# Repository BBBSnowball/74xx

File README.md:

RISC-V core made of 7400-series logic
=====================================

We take the SERV RISC-V core and map it to 74xx logic with
tools that were intended for FPGA/ASIC synthesis. A PCB is
sort-of like an ASIC in 127000 nm technology, right?

Before you expect too much:
1. The example PCB has been designed for its artistic value.
   It won't work as-is (see below).
2. You can use the tools with your logic (Verilog, VHDL) but
   you may have to adjust the scripts a bit. In addition,
   some manual work in KiCad will be required, e.g. add
   connectors or LEDs.
3. The automated part is from Verilog to PCB. All further
   steps for the example image above are manual work in
   GIMP and Inkscape. See below for some info about that.

Why?
----

Olof was presenting the serv core at a virtual RISC-V meetup
in 2021. He mentioned that someone had converted it to 74xx
logic and the gate count was low enough that I just *might*
be able to afford building one. He pointed me to
[this](https://web.archive.org/web/20200930140306/https://twitter.com/ravenslofty/status/1311285303236268033)
Twitter thread by ravenslofty. Much of this project is based
on their idea.

It would be a lot of work to make a PCB that has enough educational
value to warant the cost, e.g. add RAM and peripherals and have some
programs that are small enough to somehow load onto the board and
then debug with a multimeter.

We revisited the project two years later with a more achievable
goal: Make a PCB that looks nice and sort-of could work.

How?
----

The usual small RISC-V cores need around 1000 LUT. [SERV][SERV] is
bit-serial, which is quite unusual for a 32-bit ISA, but it makes
the core really small (200 LUT).

[Yosys][Yosys] is used by most of the FOSS FPGA flows but you can point
it to other targets. Ravenslofty has created such a target description
("74xx-liberty", the main library file is in "liberty" format).
Pepijn de Vos has added scripts that convert the resulting netlist
into a KiCad schematic.

The algorithms in [Verilog to Routing][VTR]'s VPR were meant to place
and route logic in an FPGA but they will also unclutter our ratsnest
of connections. We only have to provide a description of our, ehm, "FPGA".
(It is field programmable if you bring your PineCil, isn't it?)

As this is for artistic value, we choose the aspect ratio of the FPGA
grid to fit A4 paper and there are some strategic cutouts.

We are only interested in placement but the result will be better when we
let it run routing passes anyway. The tool will generate an XML file that
tells us which gates have been combined into one logic element (i.e. one
74xx device in our case) and a text file with the positions of each
element in the grid. We generate a KiCad PCB file from that information
using [SKiDL][SKiDL].

Some parts are best designed in KiCad, e.g. keepout areas for artistic
reasons, and buttons+LEDs that should be in specific locations. Therefore,
we combine the generated parts with a template PCB.

Next, we need to route the ratsnest. We could try and use the routing
that has been generated by VPR but we don't do that, for now. Instead,
we let the [freerouting][freerouting] auto-router do all of the work.
It will finish within an hour or so if the placement is good (i.e. short
connections with not too many crossings) and if there is enough space.
If you add some huge keepout areas in the middle (why would anyone do
that? *cough*), it will stop making progress after some hours and not
finish even after days so it's best to restart with a more relaxed layout
in this case.

[SERV]: https://github.com/olofk/serv
[Yosys]: https://github.com/YosysHQ/yosys
[VTR]: https://github.com/verilog-to-routing/vtr-verilog-to-routing
[SKiDL]: https://github.com/devbisme/skidl
[freerouting]: https://github.com/freerouting/freerouting

Will the RISC-V actually work?
------------------------------

Sadly, no. And for more than one reason. Most of this is because we ran out
of time (and correct function was optional):

1. The keepout areas were too much for the auto-router. 200 connections (5%)
   are unrouted. It did work with an earlier version (`serv_top` without
   register file and no keepouts). We think that it will work with more space
   (and maybe run VPR a few times and see how the auto-router likes each placement).
2. The register file seems to use a synchronous RAM with heterogeneous widths
   and the polarity of some control signals doesn't match. We will have to
   provide a wrapper that adds the required glue logic.
3. Instruction and data bus are mapped to DIP switches and LEDs so the processor
   won't run very far unless you answer its questions for values from the RAM.
   This is technically a working processor and it sidesteps the issue of how
   we would bootstrap (i.e. load the initial program into RAM). The downside is
   that nobody will use it for very long. Any practical PCB would use something
   like the Servant SoC and add UART and a bootloader in ROM (or a large array
   of DIP switches - if you have plenty of time and money to spare).
4. Crosstalk may be an issue even at small speeds if we inject false edges into
   the clock or reset lines. Fortunately, these should be the only critical ones
   so some shielding (or buffers) should help if we run into problems with that.
   (I don't think freerouting can do shielding but we could increase trace width
   for the net class and later replace it by a smaller wire plus shields.)
5. We haven't simulated the result and what isn't tested usually doesn't work.
   I don't expect any significant bugs in the tools but plenty could be hiding
   in our scripts and target descriptions.
    - We already have models that should work for simulation (see `74_models.v`).
    - Proprietary ASIC flows use logic equivalence checks (Formality, Conformal).
      Yosys supports formal verification so [we could do the same](https://github.com/YosysHQ/eqy).
    - In either case, we have to map from PCB to Verilog netlist while avoiding
      doing the same errors as in the forward direction, e.g. swapped pins.
6. The image is scaled to A4 but the actual size is 510x353 mm, which is larger
   than A4 and even A3.

Other improvements that we omitted for lack of time:

- Let VPR determine the order and location or IO pads or add location constraints
  if the order is fixed.
- Tell VPR about the locations of pins in each logic element. We are currently
  telling it that pins can be swapped at will, which isn't really true.
- Use the routing info from VPR, e.g. increase grid spacing if routing channels
  are full. We could even generate wires for the routing so the auto-router has
  a working starting point for global routing (assuming that we omit connection stubs
  between routing channels and the actual devices pads because freerouting can probably
  do that better).
- Automatically call freerouting and import result.

How do I use it with my own logic?
----------------------------------

1. Install the tools.
    - If you have the Nix package manager, enable flakes and run `nix develop` in this repo.
    - Otherwise, have a look at `flake.nix` and install with a package manager of your choice.
2. Edit the scripts (optional but recommended):
    1. Point `kicad/Makefile` to your Verilog and/ or VHDL files.
        - Let's keep the "serv" name, for now, to keep it simple.
        - For VHDL, you will need Yosys with the GHDL plugin.
    2. Adjust the FPGA grid.
        - Change one of the `<fixed_layout>` nodes in `kicad/74xx_fpga.xml`
          and put its name into the Makefile after the `--device` parameter for VPR.
        - Keep the grid only a bit larger than necessary if you want to achieve high
            utilization (i.e. not so many unused gates).
        - Update the grid size argument for `generate_netlist2.py` in the Makefile.
            You can use the empty string to automatically use min/max occupied positions.
    3. Adjust the KiCad template (`kicad/serv_vpr_template.kicad_pcb`).
        - If you don't want any custom features for you PCB, you can pass an empty
          string to `generate_netlist2.py` instead of template file to not use any template.
        - We will use the auto-router anyway so there's no need to do manual routing
          for custom parts of the logic.
    4. Adjust `generate_netlist2.py` to change how the PCB is generated.
        - Grid spacing is defined in `mm_per_chip_x` and `mm_per_chip_y`.
        - Omit or move the capacitor.
        - Adjust position and layer of texts.
        - ...
3. Run `make all` (or `make out/serv_vpr_generated.kicad_pcb`). This will
   generate the PCB.
4. Run the auto-router.
    - Run `make serv-freerouting` to start the auto-router.
    - Pay attention to board edges. If part of the logic is outside the board, routing
      will never finish. If you do any manual changes in KiCad, don't forget to export
      the Spectra file, again.
    - Start auto-routing. It will usually need several passes before it has routed
      everything and then it will start optimization. If it doesn't seem to get any
      better anymore, left-click on the main area of the window to stop it. It will ask
      for confirmation and then it needs some time to actually stop.
    - Export the Spectra session and import it into KiCad.
5. Do the usual KiCad things, e.g. design rule check, export gerbers, ...

How to make a picture like the one above?
-----------------------------------------

This is not a complete guide because all of this were manual steps with lots of trial and error.

- KiCad: We have added some of the missing trace (that the auto-router could route). That's why the
  traces on the right look different.
- KiCad: Export -> SVG: F_Cu, B_C, F_Silk
    - Cu with colors, Silk in black&white
    - (reason not to export in black&white: hole in pads would be invisible (same color as the ring))
- KiCad: Open 3D view. Enable Raytracing. Export screenshots of top and bottom part of the PCB.
    - I had set many of the colors to semi-transparent for an earlier experiment but I think that I
      had undone that for the pictures.
- Load in Inkscape, select everything but background, export "Selection" to PNG with 600 dpi
    - I would like to keep it as a vector graphic but Inkscape becomes very slow.
- Import into GIMP:
    - invert colors
    - select by color with threshold 5%, click light-grey ring of a via, flood-fill with same color as the traces
    - add as layers to the same image
    - copy content of layer into layer mask, invert colors, use Colors->Curve to make the main color fully opaque
    - add a white background layer
    - copy bottom and upper part from renderings, adjust scale and position to match copper layers
- Colors and 3D effect for copper layers:
    - The geometry is in the layer mask so we can simple fill the whole layer with the desired color.
    - Fill F_Cu with Perlin noise: Filters -> Render -> Noise -> Perlin
      (I haven't written down the settings. Current settings are: alpha 1.2, scale 1.8, z -1.0, iterations 3)
    - Change color (done with Colors -> Colorize, I think).
    - Fill B_Cu with a darker shade of red.
    - Copy F_Cu, rename to "F_Cu shadow", between F_Cu and B_Cu, move down and right by a few pixels.
      Fill with a darker shade of red.
        - I had the layer mode set to "darken" and that looked a bit better. However, it was only applied
          to layers in the same group so that became an issue later.
- White background for Silk:
    - Layer mask to selection for Silk layer.
    - Add a new layer below Silk.
    - Grow and/ or feather the selection.
    - Fill whole selection with white.
    - Repeat with different settings until it looks right.
- Blend between copper and renderings:
    - Add silk layers to one layer group and copper layers to another.
    - It might make sense to do the same for the renderings (or combine them into one layer).
    - Extend rendering layers to image size.
    - Edit layer masks. Use gradient fill for the general shape of the blending.
    - Use airbrush tool for the details.
        - Make the edges of the blend not to straight.
        - Darken or remove copper over ICs and capacitors (at least were it looks strange).
        - Extend some of the copper traces over the renderings.
        - Silk is black in the middle part and white on the renderings. For any text that crosses the blending,
          make Silk layer opaque for that whole text.
- Add large digits:
    - select the wires and/ or areas in KiCad so they are painted in front of other things (e.g. airwires)
    - copy screenshot into GIMP
    - select wanted parts (select by color)
    - copy into main image as a new layer, adjust scale and position
    - select by color, feather by 50 px, fill with yellow, feather by 150 px (probably twice),
      fill with white (or very light yellow), choose sensible opacity for the layer
    - This is not just to make the inner ring of the zero visible but also to de-emphasize some tracks that
      run through the supposed keepout areas (because I had hoped that it would be able to route it without
      the keepouts but it didn't make much progress because any new trace would have to ripup lots of existing
      ones). Thus, it should be in front of the copper layers.
- Brighten area for prior work text:
    - Add a layer. Rectangular selection. Grow/feather. Fill with white. Set sensible opacity.
- Fixup texts on Silk:
    - Some important texts are hidden behind LEDs or missing (wrong layer?).
    - We didn't want to redo the renderings so we added texts in GIMP. Font is wrong, perspective is wrong, color
      doesn't quite match. Well, close enough.
- Add border:
    - The copper layers contain the board edge but that doesn't look nice.
    - The aspect ratio doesn't exactly match A4 so we will have some white space around our image. The renderings
      have a defined edge but the copper layers not so much.
    - Therefore, add a black border around everything.
- Export PNG
    - Use same DPI as before.
- Inkscape:
    - New A4 document.
    - Add the image and choose sensible page borders so the difference in aspect ratio is not too visible.
    - Add texts. The 7-segment font is [DSEG](https://www.keshikan.net/fonts-e.html).
    - Add QR code (`qrencode -t png -o qrcode.png 'https://github.com/BBBSnowball/74xx/tree/hans'`).
- Export text to GIMP:
    - This is only because further processing is out of our hands and we want to reduce risk. A PNG seems to
      be the safest bet with the image being mostly non-vector anyway.
    - Select the image. Set page size to content (i.e. the selected image).
    - Hide the image (using the "Layers and Objects" dialog).
    - Export to PNG using exactly the resolution of the image in GIMP.
      (DPI won't match because we have scaled the image in Inkscape.)
    - Add as a layer in GIMP.
    - Export PNG from GIMP.

The resulting XCF file is 500 MB in size so each download would be half of the free, monthly quota on Github.
We will have to find some other way to share it...

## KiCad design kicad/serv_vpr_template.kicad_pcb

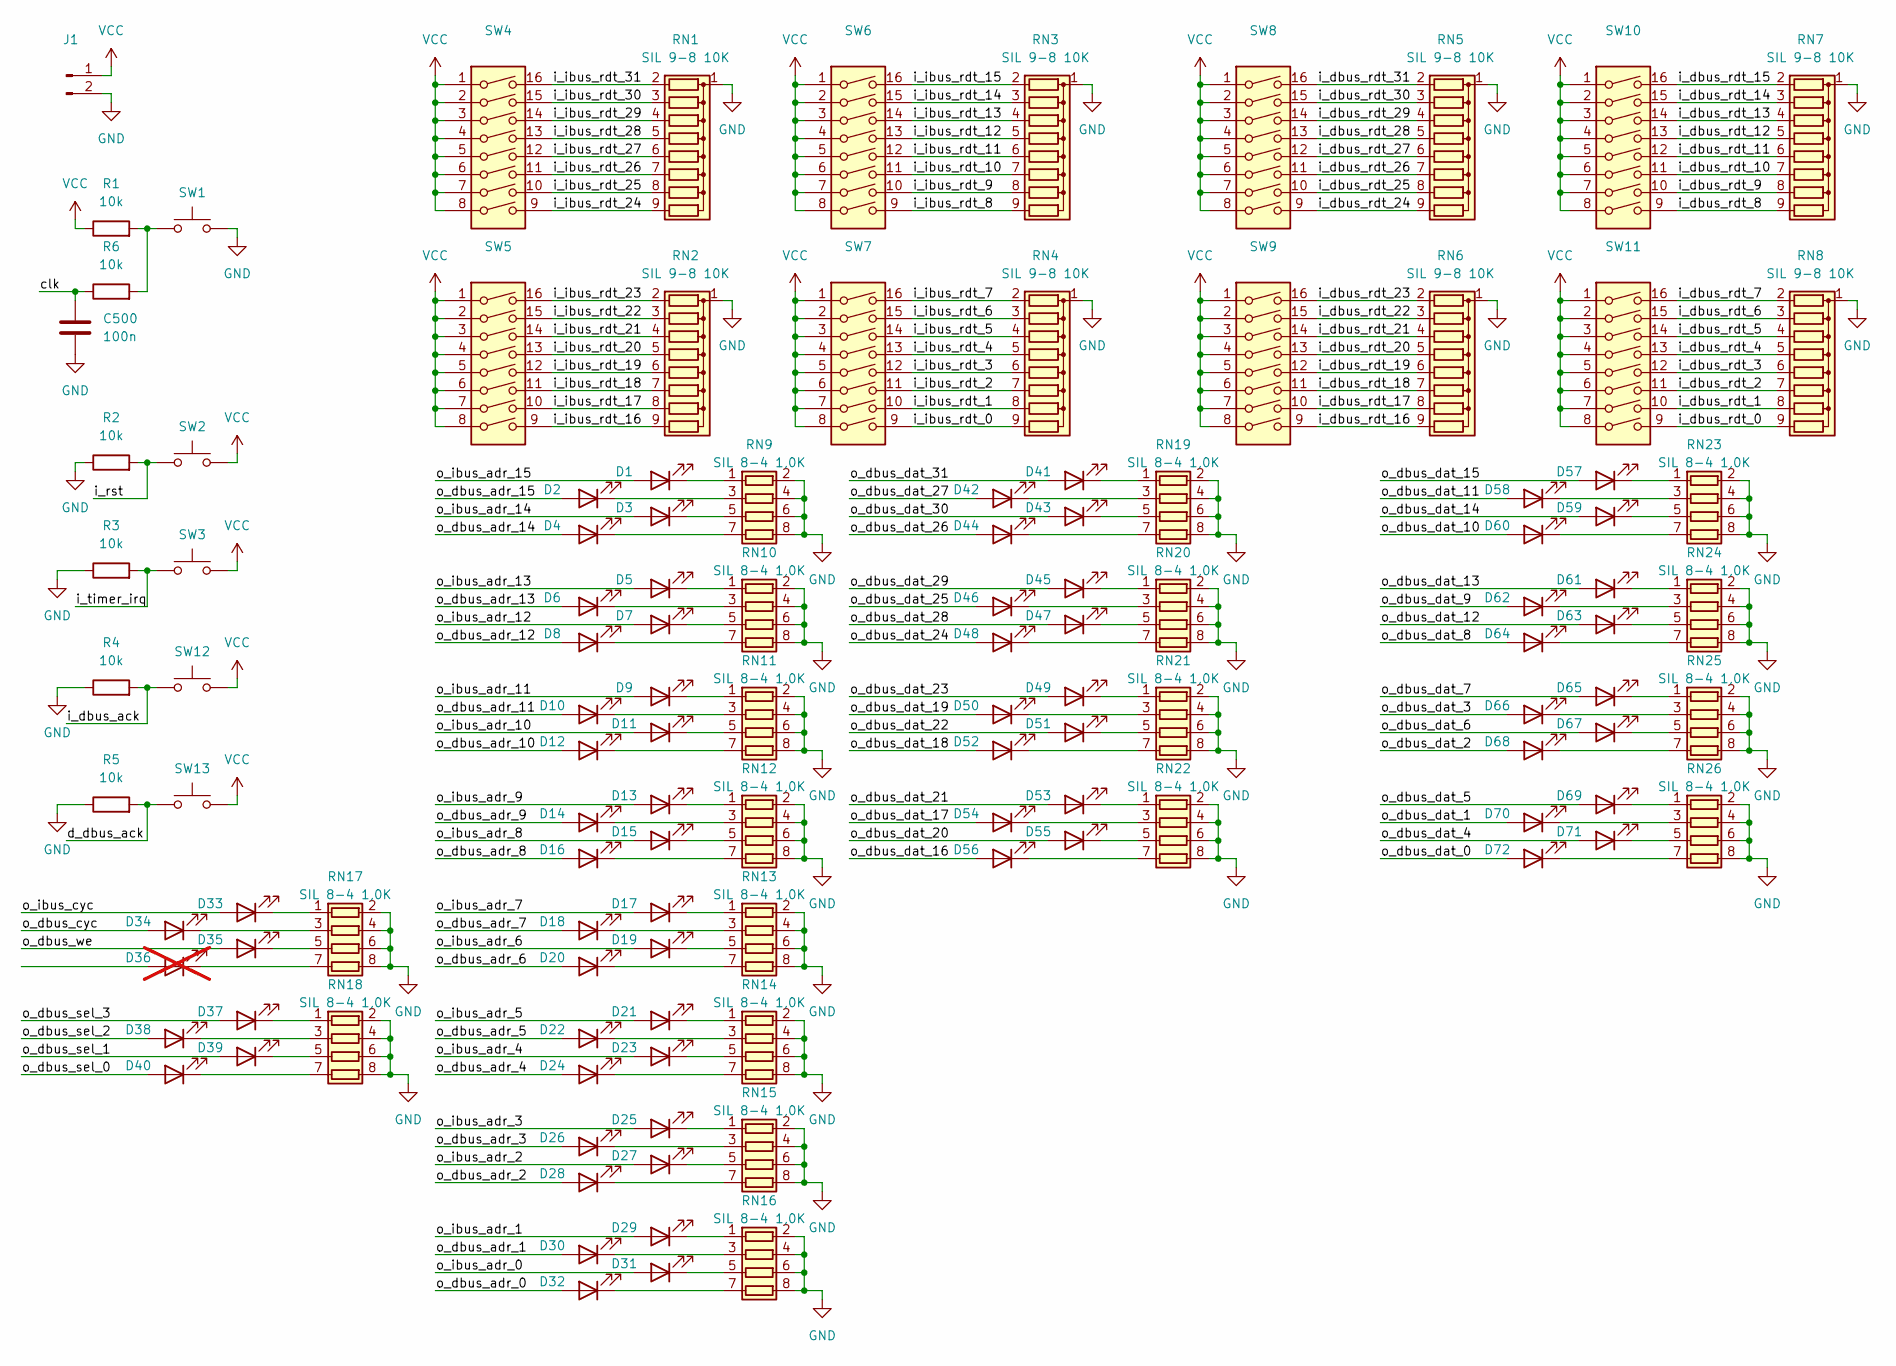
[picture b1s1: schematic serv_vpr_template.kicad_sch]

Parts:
C500: 100n; C_Disc_D5.1mm_W3.2mm_P5.00mm
D1, D2, D3, D4, D5, D6, D7, D8, D9, D10, D11, D12, D13, D14, D15, D16, D17, D18, D19, D20, D21, D22, D23, D24, D25, D26, D27, D28, D29, D30, D31, D32, D33, D34, D35, D37, D38, D39, D40, D41, D42, D43, D44, D45, D46, D47, D48, D49, D50, D51, D52, D53, D54, D55, D56, D57, D58, D59, D60, D61, D62, D63, D64, D65, D66, D67, D68, D69, D70, D71, D72: LED_D5.0mm
D36: LED_D5.0mm; not fitted
J1: Conn_01x02_Pin; Wago_734-132_1x02_P3.50mm_Vertical
R1, R2, R3, R4, R5, R6: 10k; R_Axial_DIN0207_L6.3mm_D2.5mm_P10.16mm_Horizontal
RN1, RN2, RN3, RN4, RN5, RN6, RN7, RN8: SIL 9-8 10K; R_Array_SIP9
RN9, RN10, RN11, RN12, RN13, RN14, RN15, RN16, RN17, RN18, RN19, RN20, RN21, RN22, RN23, RN24, RN25, RN26: SIL 8-4 1,0K; R_Array_SIP8
SW1, SW2, SW3, SW12, SW13: SW_PUSH_6mm_H5mm
SW4, SW5, SW6, SW7, SW8, SW9, SW10, SW11: SW_DIP_SPSTx08_Slide_9.78x22.5mm_W7.62mm_P2.54mm

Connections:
/clk: C500.1, R6.1
/d_dbus_ack: R5.2, SW13.1
/i_dbus_ack: R4.2, SW12.1
/i_dbus_rdt_0: RN8.9 (R8), SW11.9
/i_dbus_rdt_1: RN8.8 (R7), SW11.10
/i_dbus_rdt_2: RN8.7 (R6), SW11.11
/i_dbus_rdt_3: RN8.6 (R5), SW11.12
/i_dbus_rdt_4: RN8.5 (R4), SW11.13
/i_dbus_rdt_5: RN8.4 (R3), SW11.14
/i_dbus_rdt_6: RN8.3 (R2), SW11.15
/i_dbus_rdt_7: RN8.2 (R1), SW11.16
/i_dbus_rdt_8: RN7.9 (R8), SW10.9
/i_dbus_rdt_9: RN7.8 (R7), SW10.10
/i_dbus_rdt_10: RN7.7 (R6), SW10.11
/i_dbus_rdt_11: RN7.6 (R5), SW10.12
/i_dbus_rdt_12: RN7.5 (R4), SW10.13
/i_dbus_rdt_13: RN7.4 (R3), SW10.14
/i_dbus_rdt_14: RN7.3 (R2), SW10.15
/i_dbus_rdt_15: RN7.2 (R1), SW10.16
/i_dbus_rdt_16: RN6.9 (R8), SW9.9
/i_dbus_rdt_17: RN6.8 (R7), SW9.10
/i_dbus_rdt_18: RN6.7 (R6), SW9.11
/i_dbus_rdt_19: RN6.6 (R5), SW9.12
/i_dbus_rdt_20: RN6.5 (R4), SW9.13
/i_dbus_rdt_21: RN6.4 (R3), SW9.14
/i_dbus_rdt_22: RN6.3 (R2), SW9.15
/i_dbus_rdt_23: RN6.2 (R1), SW9.16
/i_dbus_rdt_24: RN5.9 (R8), SW8.9
/i_dbus_rdt_25: RN5.8 (R7), SW8.10
/i_dbus_rdt_26: RN5.7 (R6), SW8.11
/i_dbus_rdt_27: RN5.6 (R5), SW8.12
/i_dbus_rdt_28: RN5.5 (R4), SW8.13
/i_dbus_rdt_29: RN5.4 (R3), SW8.14
/i_dbus_rdt_30: RN5.3 (R2), SW8.15
/i_dbus_rdt_31: RN5.2 (R1), SW8.16
/i_ibus_rdt_0: RN4.9 (R8), SW7.9
/i_ibus_rdt_1: RN4.8 (R7), SW7.10
/i_ibus_rdt_2: RN4.7 (R6), SW7.11
/i_ibus_rdt_3: RN4.6 (R5), SW7.12
/i_ibus_rdt_4: RN4.5 (R4), SW7.13
/i_ibus_rdt_5: RN4.4 (R3), SW7.14
/i_ibus_rdt_6: RN4.3 (R2), SW7.15
/i_ibus_rdt_7: RN4.2 (R1), SW7.16
/i_ibus_rdt_8: RN3.9 (R8), SW6.9
/i_ibus_rdt_9: RN3.8 (R7), SW6.10
/i_ibus_rdt_10: RN3.7 (R6), SW6.11
/i_ibus_rdt_11: RN3.6 (R5), SW6.12
/i_ibus_rdt_12: RN3.5 (R4), SW6.13
/i_ibus_rdt_13: RN3.4 (R3), SW6.14
/i_ibus_rdt_14: RN3.3 (R2), SW6.15
/i_ibus_rdt_15: RN3.2 (R1), SW6.16
/i_ibus_rdt_16: RN2.9 (R8), SW5.9
/i_ibus_rdt_17: RN2.8 (R7), SW5.10
/i_ibus_rdt_18: RN2.7 (R6), SW5.11
/i_ibus_rdt_19: RN2.6 (R5), SW5.12
/i_ibus_rdt_20: RN2.5 (R4), SW5.13
/i_ibus_rdt_21: RN2.4 (R3), SW5.14
/i_ibus_rdt_22: RN2.3 (R2), SW5.15
/i_ibus_rdt_23: RN2.2 (R1), SW5.16
/i_ibus_rdt_24: RN1.9 (R8), SW4.9
/i_ibus_rdt_25: RN1.8 (R7), SW4.10
/i_ibus_rdt_26: RN1.7 (R6), SW4.11
/i_ibus_rdt_27: RN1.6 (R5), SW4.12
/i_ibus_rdt_28: RN1.5 (R4), SW4.13
/i_ibus_rdt_29: RN1.4 (R3), SW4.14
/i_ibus_rdt_30: RN1.3 (R2), SW4.15
/i_ibus_rdt_31: RN1.2 (R1), SW4.16
/i_rst: R2.2, SW2.1
/i_timer_irq: R3.2, SW3.1
/o_dbus_adr_0: D32.2 (A)
/o_dbus_adr_1: D30.2 (A)
/o_dbus_adr_2: D28.2 (A)
/o_dbus_adr_3: D26.2 (A)
/o_dbus_adr_4: D24.2 (A)
/o_dbus_adr_5: D22.2 (A)
/o_dbus_adr_6: D20.2 (A)
/o_dbus_adr_7: D18.2 (A)
/o_dbus_adr_8: D16.2 (A)
/o_dbus_adr_9: D14.2 (A)
/o_dbus_adr_10: D12.2 (A)
/o_dbus_adr_11: D10.2 (A)
/o_dbus_adr_12: D8.2 (A)
/o_dbus_adr_13: D6.2 (A)
/o_dbus_adr_14: D4.2 (A)
/o_dbus_adr_15: D2.2 (A)
/o_dbus_cyc: D34.2 (A)
/o_dbus_dat_0: D72.2 (A)
/o_dbus_dat_1: D70.2 (A)
/o_dbus_dat_2: D68.2 (A)
/o_dbus_dat_3: D66.2 (A)
/o_dbus_dat_4: D71.2 (A)
/o_dbus_dat_5: D69.2 (A)
/o_dbus_dat_6: D67.2 (A)
/o_dbus_dat_7: D65.2 (A)
/o_dbus_dat_8: D64.2 (A)
/o_dbus_dat_9: D62.2 (A)
/o_dbus_dat_10: D60.2 (A)
/o_dbus_dat_11: D58.2 (A)
/o_dbus_dat_12: D63.2 (A)
/o_dbus_dat_13: D61.2 (A)
/o_dbus_dat_14: D59.2 (A)
/o_dbus_dat_15: D57.2 (A)
/o_dbus_dat_16: D56.2 (A)
/o_dbus_dat_17: D54.2 (A)
/o_dbus_dat_18: D52.2 (A)
/o_dbus_dat_19: D50.2 (A)
/o_dbus_dat_20: D55.2 (A)
/o_dbus_dat_21: D53.2 (A)
/o_dbus_dat_22: D51.2 (A)
/o_dbus_dat_23: D49.2 (A)
/o_dbus_dat_24: D48.2 (A)
/o_dbus_dat_25: D46.2 (A)
/o_dbus_dat_26: D44.2 (A)
/o_dbus_dat_27: D42.2 (A)
/o_dbus_dat_28: D47.2 (A)
/o_dbus_dat_29: D45.2 (A)
/o_dbus_dat_30: D43.2 (A)
/o_dbus_dat_31: D41.2 (A)
/o_dbus_sel_0: D40.2 (A)
/o_dbus_sel_1: D39.2 (A)
/o_dbus_sel_2: D38.2 (A)
/o_dbus_sel_3: D37.2 (A)
/o_dbus_we: D35.2 (A)
/o_ibus_adr_0: D31.2 (A)
/o_ibus_adr_1: D29.2 (A)
/o_ibus_adr_2: D27.2 (A)
/o_ibus_adr_3: D25.2 (A)
/o_ibus_adr_4: D23.2 (A)
/o_ibus_adr_5: D21.2 (A)
/o_ibus_adr_6: D19.2 (A)
/o_ibus_adr_7: D17.2 (A)
/o_ibus_adr_8: D15.2 (A)
/o_ibus_adr_9: D13.2 (A)
/o_ibus_adr_10: D11.2 (A)
/o_ibus_adr_11: D9.2 (A)
/o_ibus_adr_12: D7.2 (A)
/o_ibus_adr_13: D5.2 (A)
/o_ibus_adr_14: D3.2 (A)
/o_ibus_adr_15: D1.2 (A)
/o_ibus_cyc: D33.2 (A)
GND: C500.2, J1.2, R2.1, R3.1, R4.1, R5.1, RN1.1 (common), RN2.1 (common), RN3.1 (common), RN4.1 (common), RN5.1 (common), RN6.1 (common), RN7.1 (common), RN8.1 (common), RN9.2 (R1.2), RN9.4 (R2.2), RN9.6 (R3.2), RN9.8 (R4.2), RN10.2 (R1.2), RN10.4 (R2.2), RN10.6 (R3.2), RN10.8 (R4.2), RN11.2 (R1.2), RN11.4 (R2.2), RN11.6 (R3.2), RN11.8 (R4.2), RN12.2 (R1.2), RN12.4 (R2.2), RN12.6 (R3.2), RN12.8 (R4.2), RN13.2 (R1.2), RN13.4 (R2.2), RN13.6 (R3.2), RN13.8 (R4.2), RN14.2 (R1.2), RN14.4 (R2.2), RN14.6 (R3.2), RN14.8 (R4.2), RN15.2 (R1.2), RN15.4 (R2.2), RN15.6 (R3.2), RN15.8 (R4.2), RN16.2 (R1.2), RN16.4 (R2.2), RN16.6 (R3.2), RN16.8 (R4.2), RN17.2 (R1.2), RN17.4 (R2.2), RN17.6 (R3.2), RN17.8 (R4.2), RN18.2 (R1.2), RN18.4 (R2.2), RN18.6 (R3.2), RN18.8 (R4.2), RN19.2 (R1.2), RN19.4 (R2.2), RN19.6 (R3.2), RN19.8 (R4.2), RN20.2 (R1.2), RN20.4 (R2.2), RN20.6 (R3.2), RN20.8 (R4.2), RN21.2 (R1.2), RN21.4 (R2.2), RN21.6 (R3.2), RN21.8 (R4.2), RN22.2 (R1.2), RN22.4 (R2.2), RN22.6 (R3.2), RN22.8 (R4.2), RN23.2 (R1.2), RN23.4 (R2.2), RN23.6 (R3.2), RN23.8 (R4.2), RN24.2 (R1.2), RN24.4 (R2.2), RN24.6 (R3.2), RN24.8 (R4.2), RN25.2 (R1.2), RN25.4 (R2.2), RN25.6 (R3.2), RN25.8 (R4.2), RN26.2 (R1.2), RN26.4 (R2.2), RN26.6 (R3.2), RN26.8 (R4.2), SW1.2
unnamed: D1.1 (K), RN9.1 (R1.1)
unnamed: D2.1 (K), RN9.3 (R2.1)
unnamed: D3.1 (K), RN9.5 (R3.1)
unnamed: D4.1 (K), RN9.7 (R4.1)
unnamed: D5.1 (K), RN10.1 (R1.1)
unnamed: D6.1 (K), RN10.3 (R2.1)
unnamed: D7.1 (K), RN10.5 (R3.1)
unnamed: D8.1 (K), RN10.7 (R4.1)
unnamed: D9.1 (K), RN11.1 (R1.1)
unnamed: D10.1 (K), RN11.3 (R2.1)
unnamed: D11.1 (K), RN11.5 (R3.1)
unnamed: D12.1 (K), RN11.7 (R4.1)
unnamed: D13.1 (K), RN12.1 (R1.1)
unnamed: D14.1 (K), RN12.3 (R2.1)
unnamed: D15.1 (K), RN12.5 (R3.1)
unnamed: D16.1 (K), RN12.7 (R4.1)
unnamed: D17.1 (K), RN13.1 (R1.1)
unnamed: D18.1 (K), RN13.3 (R2.1)
unnamed: D19.1 (K), RN13.5 (R3.1)
unnamed: D20.1 (K), RN13.7 (R4.1)
unnamed: D21.1 (K), RN14.1 (R1.1)
unnamed: D22.1 (K), RN14.3 (R2.1)
unnamed: D23.1 (K), RN14.5 (R3.1)
unnamed: D24.1 (K), RN14.7 (R4.1)
unnamed: D25.1 (K), RN15.1 (R1.1)
unnamed: D26.1 (K), RN15.3 (R2.1)
unnamed: D27.1 (K), RN15.5 (R3.1)
unnamed: D28.1 (K), RN15.7 (R4.1)
unnamed: D29.1 (K), RN16.1 (R1.1)
unnamed: D30.1 (K), RN16.3 (R2.1)
unnamed: D31.1 (K), RN16.5 (R3.1)
unnamed: D32.1 (K), RN16.7 (R4.1)
unnamed: D33.1 (K), RN17.1 (R1.1)
unnamed: D34.1 (K), RN17.3 (R2.1)
unnamed: D35.1 (K), RN17.5 (R3.1)
unnamed: D37.1 (K), RN18.1 (R1.1)
unnamed: D38.1 (K), RN18.3 (R2.1)
unnamed: D39.1 (K), RN18.5 (R3.1)
unnamed: D40.1 (K), RN18.7 (R4.1)
unnamed: D41.1 (K), RN19.1 (R1.1)
unnamed: D42.1 (K), RN19.3 (R2.1)
unnamed: D43.1 (K), RN19.5 (R3.1)
unnamed: D44.1 (K), RN19.7 (R4.1)
unnamed: D45.1 (K), RN20.1 (R1.1)
unnamed: D46.1 (K), RN20.3 (R2.1)
unnamed: D47.1 (K), RN20.5 (R3.1)
unnamed: D48.1 (K), RN20.7 (R4.1)
unnamed: D49.1 (K), RN21.1 (R1.1)
unnamed: D50.1 (K), RN21.3 (R2.1)
unnamed: D51.1 (K), RN21.5 (R3.1)
unnamed: D52.1 (K), RN21.7 (R4.1)
unnamed: D53.1 (K), RN22.1 (R1.1)
unnamed: D54.1 (K), RN22.3 (R2.1)
unnamed: D55.1 (K), RN22.5 (R3.1)
unnamed: D56.1 (K), RN22.7 (R4.1)
unnamed: D57.1 (K), RN23.1 (R1.1)
unnamed: D58.1 (K), RN23.3 (R2.1)
unnamed: D59.1 (K), RN23.5 (R3.1)
unnamed: D60.1 (K), RN23.7 (R4.1)
unnamed: D61.1 (K), RN24.1 (R1.1)
unnamed: D62.1 (K), RN24.3 (R2.1)
unnamed: D63.1 (K), RN24.5 (R3.1)
unnamed: D64.1 (K), RN24.7 (R4.1)
unnamed: D65.1 (K), RN25.1 (R1.1)
unnamed: D66.1 (K), RN25.3 (R2.1)
unnamed: D67.1 (K), RN25.5 (R3.1)
unnamed: D68.1 (K), RN25.7 (R4.1)
unnamed: D69.1 (K), RN26.1 (R1.1)
unnamed: D70.1 (K), RN26.3 (R2.1)
unnamed: D71.1 (K), RN26.5 (R3.1)
unnamed: D72.1 (K), RN26.7 (R4.1)
unnamed: R1.2, R6.2, SW1.1
unnamed: D36.1 (K), RN17.7 (R4.1)
VCC: J1.1, R1.1, SW2.2, SW3.2, SW4.1, SW4.2, SW4.3, SW4.4, SW4.5, SW4.6, SW4.7, SW4.8, SW5.1, SW5.2, SW5.3, SW5.4, SW5.5, SW5.6, SW5.7, SW5.8, SW6.1, SW6.2, SW6.3, SW6.4, SW6.5, SW6.6, SW6.7, SW6.8, SW7.1, SW7.2, SW7.3, SW7.4, SW7.5, SW7.6, SW7.7, SW7.8, SW8.1, SW8.2, SW8.3, SW8.4, SW8.5, SW8.6, SW8.7, SW8.8, SW9.1, SW9.2, SW9.3, SW9.4, SW9.5, SW9.6, SW9.7, SW9.8, SW10.1, SW10.2, SW10.3, SW10.4, SW10.5, SW10.6, SW10.7, SW10.8, SW11.1, SW11.2, SW11.3, SW11.4, SW11.5, SW11.6, SW11.7, SW11.8, SW12.2, SW13.2

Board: 2 copper layers, 118 parts (0 on the bottom side), 143 nets, no tracks yet.

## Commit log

2021-11-17 quick&dirty edit for current LCSC prices and availability and newer Yosys
    -> 1313 gates, $47.98
2021-11-17 adapt costs for JLC PCBA
    -> 1202 gates, $52.89
2021-11-17 generate netlist of SERV for Kicad
2021-11-19 first tests with placement by VPR
2021-11-19 copy custom_sbloc.xml from VTR
2021-11-19 use custom "FPGA" description
2021-11-19 add clock to DFF model
2021-11-19 remove constant inputs, better pictures
2021-11-19 try and optimize for area even more -> still uses 450 chips instead of 350
2021-11-19 add some fixed layouts
2023-11-18 old changes
2023-11-18 add vpr.nix, copied from dev/nix/shell.nix in vtr source
2023-11-18 change absolute paths in Makefile
2023-11-18 fix remaining issues in vpr.nix
2023-11-18 add vpr to shell.nix
2023-11-18 convert shell.nix to flake
2023-11-18 fixup: another absolute path
2023-11-18 refactor Makefile
2023-11-19 generate netlist from VPR output (only clb assignments, no position yet)
2023-11-19 add kinet2pcb
2023-11-19 copy newest version of kinet2pcb into project
2023-11-19 make kinet2pcb work with old skidl and use it in generate_netlist2.py
2023-11-19 undo part of the changes
    The AttributeError was due to `pin.ref`, not FindFootprintByReference. In addition, we have fixed the fp-lib-table issue (now that we have the code local anyway).
2023-11-19 set positions of footprints in generated Kicad PCB
2023-11-19 fixup: some lines in placement file have two tabs after name
2023-11-19 add some text
2023-11-19 set unused inputs to GND
2023-11-19 add some signal names to silk
2023-11-19 use skidl circuit for adding net names to silk
2023-11-19 improve signal labels, add edge cuts
2023-11-19 add capacitors
2023-11-19 add example PCB after auto-routing
2023-11-23 optimize positions
2023-11-23 generate Kicad file from template
2023-11-24 add big number to layout
2023-11-24 put output files into subdir
2023-11-24 add comment for FPGA layout
2023-11-24 fixup
2023-11-24 add (very rough) keepout to template
2023-11-24 move vpr.nix
2023-11-24 add package for freerouting
2023-11-24 improve keepout zones
    - left zone generated from outer hull of two lines
    - right zone: ellipse in Inkscape (77.1 x 120 mm), export to DXF
    (R14, with LWPOLYLINE), import, ungroup, zone from outer hull
    (center line would be more accurate but doesn't work)
2023-11-24 change FPGA definition
    - make switches bidirectional
    - add io_in and io_out tile type (unused, for now)
    - add clock mode for io
    - mark clb inputs as not swappable
2023-11-24 set interconnect type to "complete" for CLBs
    We don't really care, which pin is connected to which.
2023-11-25 set full connections to neighboring channels (1=100%)
2023-11-25 set default_fc and switchblock_locations
2023-11-25 try and keep left and right edge free to hopefully fix connection errors
2023-11-25 enable routing again
2023-11-25 add enough delay info for vpr to not fail
2023-11-25 add one more level of pb_type - only for xor2, so far
    I'm not sure why this makes a difference but the result is that sum_pin_class starts doing useful things for our clb and the feasibility check doesn't fail anymore.
2023-11-25 apply two-level pb_type structure for all the clb modes
2023-11-25 try to find a workaround for assertion failure in vpr
2023-11-25 actual workaround for vpr assertion failure
2023-11-25 adjust grid size, again
2023-11-25 add serv as a submodule
2023-11-25 update serv
2023-11-25 hide reference text of caps
2023-11-25 add register file
2023-11-25 add larger layout (because we need more CLBs)
2023-11-25 add more IO things to template
2023-11-26 add remaining IOs to template
2023-11-26 add support for RAM to generate_netlist2.py (IDT7132_1x1MEM8)
2023-11-27 fix support for IDT7132 when generating Kicad netlist
2023-11-27 move upper part of template up by one row
2023-11-28 connect inputs and outputs to nets in template pcb
2023-11-28 fix position of RAM
2023-11-28 bugfix: sub-blocks were ignored
    We had added another level of nesting to work around crashes in vpr.
2023-11-28 connect ibus/dbus read data in template
2023-12-03 add copy of final generated PCB
2023-12-03 add some images
2023-12-03 remove old files
2023-12-08 add images
    The XCF file is omitted due to Github's size limits.
2023-12-09 add README
2024-03-12 add link to Twitter thread
    I didn't find it in browser history when I was looking for it; but
    it turns out that the tab was still open - thanks to Tree Style Tabs
    and me not cleaning up tabs all too often ;-)
